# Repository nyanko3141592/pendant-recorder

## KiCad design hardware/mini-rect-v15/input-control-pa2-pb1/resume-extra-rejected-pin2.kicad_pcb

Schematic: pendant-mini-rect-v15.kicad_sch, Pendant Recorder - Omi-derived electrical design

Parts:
C1, C2, C3, C6, C9, C22, C26: 100n; C_0402_1005Metric
C4: 10u; C_0603_1608Metric
C5: 4.7u; C_0603_1608Metric
C7, C16, C25: 1u; C_0402_1005Metric
C11, C12: 10p tentative; C_0402_1005Metric
C13: 2.2u 10V; C_0402_1005Metric
C14: 2.2u; C_0402_1005Metric
C15: 10u 10V effective >=1u; C_0603_1608Metric
C27: 4.7u effective TBD; C_0603_1608Metric
C28: 10n; C_0402_1005Metric
C29, C32, C33: 100n 10V; C_0402_1005Metric
C30: 50p 50V C0G; C_0402_1005Metric
C31: 1u 10V; C_0402_1005Metric
D6: amber LED 0402 TBD; LED_0402_1005Metric
J1: USB4105-GF-A (candidate); USB_C_GCT_USB4105_GroundLand112
J2: Molex781710003 / DTP401525-XE; Molex_Pico-EZmate_78171-0003_1x03-1MP_P1.20mm_Vertical
J3: TC2030 SWD target pads; Tag-Connect_TC2030-IDC-NL_2x03_P1.27mm_Vertical
J4: DM3D-SF candidate; DM3D_SF_reviewed_candidate
Q3: 2N7002 (VBUS detect); SOT-23
Q4, Q5, Q6, Q7: 2N7002; SOT-23
R1: 0R; R_0402_1005Metric
R2: 10k; R_0402_1005Metric
R3, R4, R12, R13, R15, R22, R36: 100k; R_0402_1005Metric
R6, R7: 5.1k 1%; R_0402_1005Metric
R10: 6.8k 1%; R_0402_1005Metric
R11, R39: 20k 1%; R_0402_1005Metric
R14: 1M; R_0402_1005Metric
R21, R23: 22R tentative; R_0402_1005Metric
R24, R25, R28, R29, R30: 47k; R_0402_1005Metric
R32: 6.8k tentative; R_0402_1005Metric
R33, R34: 1M 1%; R_0402_1005Metric
R35, R43, R47, R48: 10k 1%; R_0402_1005Metric
R37, R38, R40, R45, R46, R49, R50: 100k 1%; R_0402_1005Metric
R41: 7.5k 1%; R_0402_1005Metric
R42: 130k 1%; R_0402_1005Metric
R44: 390k 1%; R_0402_1005Metric
SW1: B3U-1000P (candidate); SW_SPST_B3U-1000P
TH1: NCP18XH103F03RB 10k 1% B3380 candidate; R_0603_1608Metric
TP1, TP2, TP3, TP5, TP6: TestPoint; TestPoint_Pad_D1.0mm
U1: STM32U535CEU6; QFN-48-1EP_7x7mm_P0.5mm_EP5.6x5.6mm
U2: USBLC6-2P6; SOT-666
U3: BQ25185DLHR; Texas_DLH0010A_WSON-10-1EP_2.2x2mm_P0.4mm_EP0.9x1.5mm
U4: TPS7A0233PDBVR; SOT-23-5
U8: IM69D130V01XTSA1; IM69D130_JLC_SMD_trial
U10: TPS22916CYFPR; TPS22916_YFP4
U12: TLV7042DDFR; SOT-23-8
U13: MAX4995CAUT+T; SOT-23-6
U14: SN74HCS74DYYR; Texas_DYY0014A
U15: TLV803EB29DBZR; SOT-23
Y1: 32.768kHz CL=7pF TBD; Crystal_SMD_2012-2Pin_2.0x1.2mm

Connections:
/BAT: C14.1, J2.1 (PACK_PLUS), R33.1, TP1.1, U3.2 (BAT)
/BAT_ADC: C28.1, R33.2, R34.1, U1.11 (PA1)
/BAT_TS: R37.2, TH1.1 (SENSE), U12.2 (INA-), U12.5 (INB+)
/BOOT0: R3.1, U1.44 (PH3)
/BUTTON_N: R4.2, SW1.1, U1.26 (PB13)
/CC1: J1.A5 (CC1), R6.1
/CC2: J1.B5 (CC2), R7.1
/CHARGER_TS: R35.1, U3.6 (TS_MR)
/CHG_ALLOW: R43.1, U1.20 (PB2)
/CHG_GUARD_GATE: Q4.1 (G), R36.1, R43.2, U12.1 (OUTA), U12.7 (OUTB)
/CHG_INHIBIT_GATE: Q4.3 (D), R12.2, U3.4 (CE_N)
/CHG_N: R11.2, U1.27 (PB14), U3.9 (STAT1)
/GND: C1.2, C2.2, C3.2, C4.2, C5.2, C6.2, C7.2, C9.2, C11.2, C12.2, C13.2, C14.2, C15.2, C16.2, C22.2, C25.2, C26.2, C27.2, C28.2, C29.2, C30.2, C31.2, C32.2, C33.2, D6.1 (K), J1.A1 (GND), J1.A12 (GND), J1.B1 (GND), J1.B12 (GND), J1.SH (SHIELD), J2.3 (PACK_MINUS), J3.5 (GND), J4.6 (VSS), J4.SH (SHELL), Q3.2 (S), Q4.2 (S), Q5.2 (S), Q6.2 (S), Q7.2 (S), R3.2, R6.2, R7.2, R10.2, R14.2, R22.2, R34.2, R35.2, R36.2, R39.2, R41.2, R42.2, R44.2, R46.2, R49.2, R50.2, SW1.2, TH1.2 (RETURN), TP6.1, U1.8 (VSSA), U1.23 (VSS), U1.35 (VSS), U1.47 (VSS), U1.49 (VSS), U2.2 (GND), U3.5 (GND), U3.11 (EP), U4.2 (GND), U8.4 (SELECT), U8.5 (GND), U10.B1 (GND), U12.4 (VEE), U13.2 (GND), U14.7 (GND), U14.11 (2CLK), U14.12 (2D), U14.13 (2CLR_N), U15.1 (GND)
/ILIM_VSET: R42.1, U3.7 (ILIM_VSET)
/ISET: C30.1, R10.1, U3.8 (ISET)
/LSE_IN: C11.1, U1.3 (PC14), Y1.1
/LSE_OUT: C12.1, U1.4 (PC15), Y1.2
/NRST: C9.1, J3.3 (nRESET), R2.2, U1.7 (NRST)
/PDM_CLK: R21.2, U8.3 (CLOCK)
/PDM_CLK_MCU: R21.1, U1.39 (PB3)
/PDM_DATA: U1.40 (PB4), U8.1 (DATA)
/SD_CLK: J4.5 (CLK), R23.2
/SD_CLK_MCU: R23.1, U1.15 (PA5)
/SD_CS_N: J4.2 (DAT3_CS), R28.2, U1.14 (PA4)
/SD_DAT1: J4.8 (DAT1), R29.2
/SD_DAT2: J4.1 (DAT2), R30.2
/SD_EN: R22.1, U1.18 (PB0), U10.B2 (ON)
/SD_MISO: J4.7 (DAT0_DO), R25.2, U1.16 (PA6)
/SD_MOSI: J4.3 (CMD_DI), R24.2, U1.17 (PA7)
/SD_V3: C26.1, C27.1, J4.4 (VDD), R24.1, R25.1, R28.1, R29.1, R30.1, TP5.1, U10.A1 (VOUT)
/STATUS_LED: R32.1, U1.29 (PA8)
/STATUS_LED_A: D6.2 (A), R32.2
/SWCLK: J3.4 (SWCLK), U1.37 (PA14)
/SWDIO: J3.2 (SWDIO), U1.34 (PA13)
/SYS: C15.1, TP2.1, U3.1 (SYS), U4.1 (IN), U4.3 (EN)
/TS_COLD_REF: R38.2, R39.1, U12.3 (INA+)
/TS_HOT_REF: R40.2, R41.1, U12.6 (INB-)
/USB_DM: J1.A7 (D-), J1.B7 (D-), U1.32 (PA11), U2.3 (IO2), U2.4 (IO2)
/USB_DP: J1.A6 (D+), J1.B6 (D+), U1.33 (PA12), U2.1 (IO1), U2.6 (IO1)
/USB_HIGH_BUDGET: Q5.1 (G), R46.1, U1.42 (PB6)
/USB_HIGH_BUDGET_DRAIN: Q5.3 (D), R45.2
/USB_ILIM_SET: R44.1, R45.1, U13.3 (SETI)
/USB_INPUT_ON: U13.4 (ON), U14.6 (1Q_N)
/USB_LATCH_CLEAR_N: Q7.3 (D), R48.2, U14.1 (1CLR_N), U15.2 (RESET_N)
/USB_LATCH_CLOCK: Q6.3 (D), R47.2, U14.3 (1CLK)
/USB_RESUME_PULSE: Q7.1 (G), R50.1, U1.2 (PC13), U1.19 (PB1)
/USB_SUSPEND_PULSE: Q6.1 (G), R49.1, U1.12 (PA2)
/V3V3: C1.1, C2.1, C3.1, C4.1, C16.1, C22.1, C25.1, J3.1 (VTref), R1.1, R2.1, R4.1, R11.1, R15.1, TP3.1, U1.1 (VBAT), U1.24 (VDD), U1.36 (VDD), U1.48 (VDD), U4.5 (OUT), U8.2 (VDD), U10.A2 (VIN)
/VBUS: C31.1, C32.1, C33.1, J1.A4 (VBUS), J1.A9 (VBUS), J1.B4 (VBUS), J1.B9 (VBUS), R13.1, R47.1, R48.1, U2.5 (VBUS), U13.5 (IN), U14.2 (1D), U14.4 (1PRE_N), U14.10 (2PRE_N), U14.14 (VCC), U15.3 (VDD)
/VBUS_GATE: Q3.1 (G), R13.2, R14.1
/VBUS_LIMITED: C13.1, C29.1, R12.1, R37.1, R38.1, R40.1, U3.10 (IN), U12.8 (VCC), U13.1 (OUT)
/VBUS_N: Q3.3 (D), R15.2, U1.10 (PA0)
/VCAP: C5.1, U1.22 (VCAP)
/VDDA: C6.1, C7.1, R1.2, U1.9 (VDDA)

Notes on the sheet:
01 MCU / RTC / UI
02 USB-C / CHARGER
03 POWER / FUEL GAUGE
04 AUDIO / SD / INDICATORS
ENGINEERING DRAFT - NOT FOR FABRICATION - See hardware/mini-rect-v15/README.md

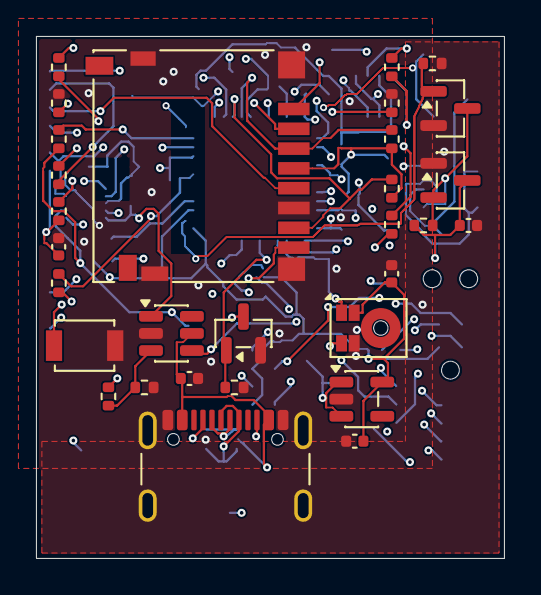
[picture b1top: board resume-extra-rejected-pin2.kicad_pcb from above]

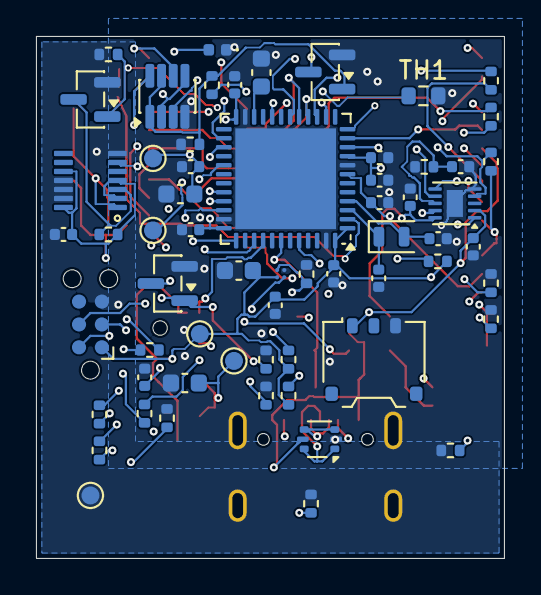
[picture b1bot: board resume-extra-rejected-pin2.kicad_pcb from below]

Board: 6 copper layers, 26.0 x 29.0 mm, 91 parts (61 on the bottom side), 54 nets.

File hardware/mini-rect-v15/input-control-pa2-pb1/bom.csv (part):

Reference,Part/value,Footprint,Design note
U1,STM32U535CEU6,Package_DFN_QFN:QFN-48-1EP_7x7mm_P0.5mm_EP5.6x5.6mm,512KB Flash/274KB RAM; non-SMPS UFQFPN48. PB3/PB4 ADF AF3; PA5/6/7 SPI1 AF5. VDD USB shared 3.3V. JLC acceptance and pin review pending.
C1,100n,Capacitor_SMD:C_0402_1005Metric,
C4,10u,Capacitor_SMD:C_0603_1608Metric,Main bulk capacitor; check startup and effective capacitance.
C9,100n,Capacitor_SMD:C_0402_1005Metric,
R2,10k,Resistor_SMD:R_0402_1005Metric,
Y1,32.768kHz CL=7pF TBD,Crystal:Crystal_SMD_2012-2Pin_2.0x1.2mm,
C11,10p tentative,Capacitor_SMD:C_0402_1005Metric,
C12,10p tentative,Capacitor_SMD:C_0402_1005Metric,
J3,TC2030 SWD target pads,Connector:Tag-Connect_TC2030-IDC-NL_2x03_P1.27mm_Vertical,TC2030-NL/CTX standard; completed STM32-compatible probe/cable; access with battery disconnected.
SW1,B3U-1000P (candidate),Button_Switch_SMD:SW_SPST_B3U-1000P,
R4,100k,Resistor_SMD:R_0402_1005Metric,
J1,USB4105-GF-A (candidate),PendantD1:USB_C_GCT_USB4105_GroundLand112,Exact footprint and shield pad numbering pending connector selection
R6,5.1k 1%,Resistor_SMD:R_0402_1005Metric,
R7,5.1k 1%,Resistor_SMD:R_0402_1005Metric,
U2,USBLC6-2P6,Package_TO_SOT_SMD:SOT-666,"ST DS4260 same 6-pin function diagram; smaller package, LCSC C15999 catalog; orientation/land pattern final audit pending."
C13,2.2u 10V,Capacitor_SMD:C_0402_1005Metric,
U3,BQ25185DLHR,Package_DFN_QFN:Texas_DLH0010A_WSON-10-1EP_2.2x2mm_P0.4mm_EP0.9x1.5mm,XE candidate4.1V ±0.5% =>4.1205V upper;44.12mA nominal charging. ILIM500 requires host power policy; thermal contact and battery capacity at4.1V unqualified; charge inhibited.
R10,6.8k 1%,Resistor_SMD:R_0402_1005Metric,XE prototype44.12mA nominal;10%IC/1%R screen39.31..49.02mA below110mA pack maximum. Nominal4.41mA termination exceeds manufacturer1.1mA reference; capacity/16h not guaranteed. No charge enable.
R11,20k 1%,Resistor_SMD:R_0402_1005Metric,
C14,2.2u,Capacitor_SMD:C_0402_1005Metric,
J2,Molex781710003 / DTP401525-XE,Connector_Molex:Molex_Pico-EZmate_78171-0003_1x03-1MP_P1.20mm_Vertical,"Pack manufacturer p9:1red+,2NTC,3black-. Header mating-view pad alignment still requires validation. Built-in NTC has no identified R-T curve; pin2 deliberately NC. Independent factory-mountedTH1 contact sensor is mandatory; no user soldering. Reverse polarity protection review pending."
R12,100k,Resistor_SMD:R_0402_1005Metric,100k VBUS pull-up defaults Q2 to charge inhibited; no MCU GPIO connection to5V.
C15,10u 10V effective >=1u,Capacitor_SMD:C_0603_1608Metric,SYS cap per TI; DC-bias capacitance must be qualified.
U4,TPS7A0233PDBVR,Package_TO_SOT_SMD:SOT-23-5,3.3V main rail: 48-pin MCU has no separate USB supply; dropout/capacity measurement required.
C16,1u,Capacitor_SMD:C_0402_1005Metric,
U8,IM69D130V01XTSA1,Pendant:IM69D130_JLC_SMD_trial,"Direct 3.3V PDM, bottom port; no AAD. 0.768MHz/decimation48 candidate for 16kHz; acoustic validation required."
R21,22R tentative,Resistor_SMD:R_0402_1005Metric,
C22,100n,Capacitor_SMD:C_0402_1005Metric,
U10,TPS22916CYFPR,Pendant:TPS22916_YFP4,Omi SD switch; power-off sequence must tristate ALL SD signals
R22,100k,Resistor_SMD:R_0402_1005Metric,
C25,1u,Capacitor_SMD:C_0402_1005Metric,
R23,22R tentative,Resistor_SMD:R_0402_1005Metric,
R24,47k,Resistor_SMD:R_0402_1005Metric,
R25,47k,Resistor_SMD:R_0402_1005Metric,
R28,47k,Resistor_SMD:R_0402_1005Metric,
C26,100n,Capacitor_SMD:C_0402_1005Metric,
C27,4.7u effective TBD,Capacitor_SMD:C_0603_1608Metric,
TP1,TestPoint,TestPoint:TestPoint_Pad_D1.0mm,
TP2,TestPoint,TestPoint:TestPoint_Pad_D1.0mm,
TP3,TestPoint,TestPoint:TestPoint_Pad_D1.0mm,
TP5,TestPoint,TestPoint:TestPoint_Pad_D1.0mm,
TP6,TestPoint,TestPoint:TestPoint_Pad_D1.0mm,
R32,6.8k tentative,Resistor_SMD:R_0402_1005Metric,"LED current target 0.1-0.2mA; verify LED Vf, daylight readability and GPIO limits"
D6,amber LED 0402 TBD,LED_SMD:LED_0402_1005Metric,"Single status/battery indicator; firmware blinks on demand, normally dark."
C2,100n,Capacitor_SMD:C_0402_1005Metric,
C3,100n,Capacitor_SMD:C_0402_1005Metric,
C5,4.7u,Capacitor_SMD:C_0603_1608Metric,
C6,100n,Capacitor_SMD:C_0402_1005Metric,
C7,1u,Capacitor_SMD:C_0402_1005Metric,
R1,0R,Resistor_SMD:R_0402_1005Metric,
R3,100k,Resistor_SMD:R_0402_1005Metric,
Q3,2N7002 (VBUS detect),Package_TO_SOT_SMD:SOT-23,
R13,100k,Resistor_SMD:R_0402_1005Metric,
R14,1M,Resistor_SMD:R_0402_1005Metric,
R15,100k,Resistor_SMD:R_0402_1005Metric,
R33,1M 1%,Resistor_SMD:R_0402_1005Metric,"Battery divider 1:2; sample after settling, calibrate with VREFINT; not coulomb counting."
R34,1M 1%,Resistor_SMD:R_0402_1005Metric,"Battery divider 1:2; sample after settling, calibrate with VREFINT; not coulomb counting."
C28,10n,Capacitor_SMD:C_0402_1005Metric,"Battery divider 1:2; sample after settling, calibrate with VREFINT; not coulomb counting."
R35,10k 1%,Resistor_SMD:R_0402_1005Metric,Holds normal TS level when released; no floating TS/TTDM in intended circuit.
R36,100k,Resistor_SMD:R_0402_1005Metric,MCU reset/high-Z defaults to no charging permission.
R37,100k 1%,Resistor_SMD:R_0402_1005Metric,Reduce thermistor excitation; 5.25V and99k gives52.99uA maximum branch current and69.60uW maximum thermistor power. Only powered from USB.
R38,100k 1%,Resistor_SMD:R_0402_1005Metric,
R39,20k 1%,Resistor_SMD:R_0402_1005Metric,Cold threshold candidate. Beta-model sensitivity is not full manufacturer R-T qualification. See temperature-screen.json.
R40,100k 1%,Resistor_SMD:R_0402_1005Metric,
R41,7.5k 1%,Resistor_SMD:R_0402_1005Metric,Hot threshold candidate. Reserve margin for contact sensor lag; physical thermal qualification required.
U12,TLV7042DDFR,Package_TO_SOT_SMD:SOT-23-8,"Open-drain wired-AND temperature permission. Either fault pulls Q4 gate low. Board NTC replaces undocumented pack NTC; exact R-T, common-mode error and thermal contact not qualified."
Q4,2N7002,Package_TO_SOT_SMD:SOT-23,"Pulls BQ25185 CE_N low only when MCU and wired-AND comparator outputs permit. R36 defaults gate low. Startup, leakage and gate-voltage behavior need review."
C29,100n 10V,Capacitor_SMD:C_0402_1005Metric,Place adjacent to U12 supply pins.
R42,130k 1%,Resistor_SMD:R_0402_1005Metric,BQ25185 Table6-1:4.1V / ILIM500. Input450/475/498mA. Requires USB preconfiguration/suspend power management; charge stays disabled pending qualification.
C30,50p 50V C0G,Capacitor_SMD:C_0402_1005Metric,BQ25185 SLUSF65B6.1.1.4 low-current <50mA recommendation; final transient behavior requires hardware test.
R43,10k 1%,Resistor_SMD:R_0402_1005Metric,MCU permission series resistor; limits current into comparator fault clamp.
J4,DM3D-SF candidate,Pendant:DM3D_SF_reviewed_candidate,"Internal microSD fitted before case closure; CD switch unused, boot card probe required. Local land candidate matches reviewed drawing, upper keepout extended0.15mm. Current procurement suffix unconfirmed. Card model and power qualification pending."
R29,47k,Resistor_SMD:R_0402_1005Metric,Unused microSD DAT input pull-up to switched rail; verify selected card specification.
R30,47k,Resistor_SMD:R_0402_1005Metric,Unused microSD DAT input pull-up to switched rail; verify selected card specification.
TH1,NCP18XH103F03RB 10k 1% B3380 candidate,Resistor_SMD:R_0603_1608Metric,Independent factory-mounted contactNTC required because pack NTC exactR-T unspecified. Electrically insulated compliant contact to pouch and retention must be engineered and tested; no ambient-only charging approval.
U13,MAX4995CAUT+T,Package_TO_SOT_SMD:SOT-23-6,Continuous input limiter; DC screen3.3V only; FLAG explicitlyNC. Not charging qualification.
U14,SN74HCS74DYYR,Pendant_Input:Texas_DYY0014A,RawVBUS retainedOFF latch; Schmitt inputs. POR/resume clearQ=0 =>Q_N enables input. Suspend clocksD=1 =>Q_N disables. UnusedFF heldclear; PRE alwayshigh.
U15,TLV803EB29DBZR,Package_TO_SOT_SMD:SOT-23,"2.93V supervisor;B40us nominal/80us maxunderdatasheetcondition. StandardDBZ pinout, NOT RDBZ or VDBZ. Initializes latch before chargerUVLO; analog startup still needs validation."
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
